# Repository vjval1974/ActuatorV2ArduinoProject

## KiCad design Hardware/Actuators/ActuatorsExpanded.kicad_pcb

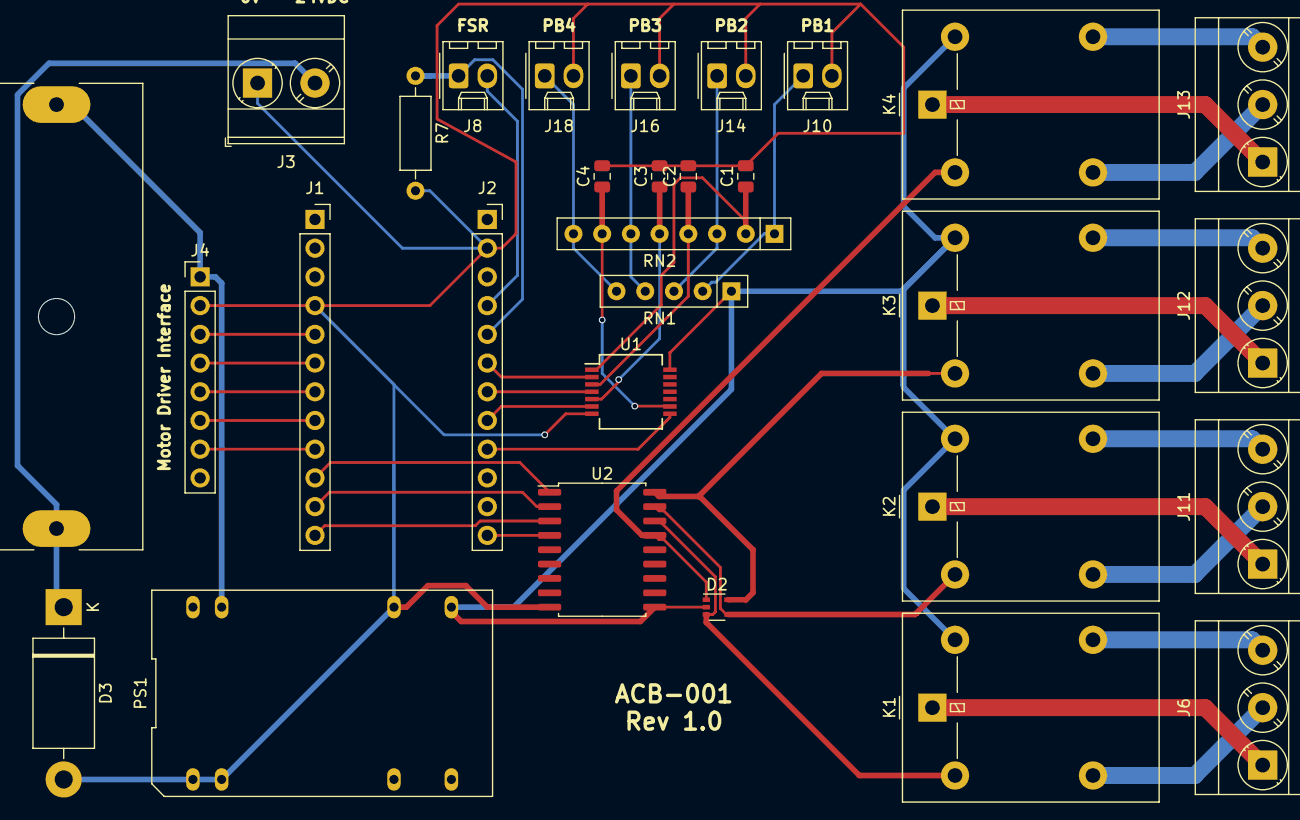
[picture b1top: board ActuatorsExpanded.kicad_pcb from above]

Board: 2 copper layers, 30 parts (0 on the bottom side), 43 nets.

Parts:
C1, C2, C3, C4: 0.1uF; C_0805_2012Metric
D2: MMBD4448HCQW; SOT-353_SC-70-5
D3: 1N5401; D_DO-201AD_P15.24mm_Horizontal
F1: 5A; Fuseholder_Cylinder-6.3x32mm_Schurter_0031-8002_Horizontal_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
J1, J2: Conn_01x12; PinSocket_1x12_P2.54mm_Vertical
J3: Screw_Terminal_01x02; TerminalBlock_Phoenix_MKDS-3-2-5.08_1x02_P5.08mm_Horizontal
J4: Conn_01x08_MountingPin; PinHeader_1x08_P2.54mm_Vertical
J6, J11, J12, J13: Screw_Terminal_01x03; TerminalBlock_Phoenix_MKDS-3-3-5.08_1x03_P5.08mm_Horizontal
J8: Conn_01x02_Female; Molex_KK-254_AE-6410-02A_1x02_P2.54mm_Vertical
J10, J14, J16, J18: Conn_01x02_Male; Molex_KK-254_AE-6410-02A_1x02_P2.54mm_Vertical
K1, K2, K3, K4: G5LE-1; Relay_SPDT_Omron-G5LE-1
PS1: TEN32411WIN; Converter_DCDC_TRACO_TEN32411
R7: 33k; R_Axial_DIN0207_L6.3mm_D2.5mm_P10.16mm_Horizontal
RN1: R_Network04; R_Array_SIP5
RN2: R_Pack04_SIP; R_Array_SIP8
U1: 74HC14; SSOP-14_5.3x6.2mm_P0.65mm
U2: ULN2803A; SOIC-18W_7.5x11.6mm_P1.27mm

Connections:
+5V: D2.2, K1.5, K2.5, K3.5, K4.5, PS1.14, RN1.1, U1.14, U2.10
+24V: F1.1, J4.1, PS1.22
GND: C1.2, C2.2, C3.2, C4.2, D3.2, J1.4, J2.2, J3.1, J4.2, J10.2, J14.2, J16.2, J18.2, PS1.2, PS1.3, PS1.16, R7.2, U1.7, U2.9
unnamed: C1.1, RN2.2, U1.1
unnamed: C2.1, RN2.4, U1.3
unnamed: C3.1, RN2.5, U1.5
unnamed: C4.1, RN2.7, U1.9
unnamed: D2.1, K4.2, U2.15
unnamed: D2.3, K1.2, U2.16
unnamed: D2.4, K2.2, U2.17
unnamed: D2.5, K3.2, U2.18
unnamed: D3.1, F1.2, J3.2
unnamed: J1.5, J4.3
unnamed: J1.6, J4.4
unnamed: J1.7, J4.5
unnamed: J1.8, J4.6
unnamed: J1.9, J4.7
unnamed: J1.10, U2.1
unnamed: J1.11, U2.2
unnamed: J1.12, U2.3
unnamed: J2.4, J8.2
unnamed: J2.5, J8.1, R7.1
unnamed: J2.6, U1.2
unnamed: J2.7, U1.4
unnamed: J2.8, U1.6
unnamed: J2.9, U1.8
unnamed: J2.12, U2.4
unnamed: J6.1, K1.1
unnamed: J6.2, K1.3
unnamed: J6.3, K1.4
unnamed: J10.1, RN1.2, RN2.1
unnamed: J11.1, K2.1
unnamed: J11.2, K2.3
unnamed: J11.3, K2.4
unnamed: J12.1, K3.1
unnamed: J12.2, K3.3
unnamed: J12.3, K3.4
unnamed: J13.1, K4.1
unnamed: J13.2, K4.3
unnamed: J13.3, K4.4
unnamed: J14.1, RN1.3, RN2.3
unnamed: J16.1, RN1.4, RN2.6
unnamed: J18.1, RN1.5, RN2.8

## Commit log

2019-09-01 Initial checkin
2019-09-02 Added motor controller class
2019-09-02 Create classes and object instantiation
2019-09-02 more OO additions
2019-09-03 Removed static variables in method
2019-09-03 Remove static variables from class methods
2019-09-03 Added debug code for state transition
2019-09-03 Set debug constant and debug code for readability
2019-09-04 monitoring settings added
2019-09-04 Pin assignment and pin-mapping fleshed out
2019-09-05 Testing Pushbuttons and wiring
2019-09-09 Tweaks for testing
2019-09-14 partial checkin. calibration code. broken build
2019-10-12 Manaul step through set up for soleniod and vacuum. Updated pins and added output code to drive solenoid/vacuum
2019-10-12 tweaking
2019-12-07 Added Hardware (Kicad)
2019-12-07 Added KiCad Project
2020-10-19 Added links to parts suppliers
2020-10-19 update to proper csv
2020-10-24 Set up CI with Azure Pipelines
    [skip ci]
2020-10-27 update diode array link
2026-05-14 Add CLAUDE.md with architecture and build guidance
    Documents the PlatformIO build/flash workflow, the DEBUG_MODE vs LOG_MODE
    build-flag toggle, and the peripheral Command/State module convention so
    future agents don't have to rediscover them from the source.
    https://claude.ai/code/session_01WQRu2yHUbYqgUTBtQG72rw
2026-05-14 Refactor: scoped enums, const-correctness, eliminate double-construction
    Behaviour-preserving cleanup based on a three-agent code review (architecture,
    embedded/AVR, OO/style). Verified by avr-g++ compile-check against the Arduino
    Leonardo variant (same ATmega32U4, same 16 MHz clock as the Pro Micro target);
    all 11 translation units compile with 0 errors.
    Changes:
    - All enums migrated to `enum class <Name> : uint8_t` and qualified at every
2026-05-14 Add native simulator + browser visualisation
    Reuses the firmware in src/ as the simulation engine: a thin Arduino.h /
    EEPROM.h shim under sim/ lets g++ build the AVR sources natively, a
    physics layer drives the sensor pins each tick, and a Python SSE server
    streams state to an HTML page. The state machine you see in the browser
    is the exact code that flashes to the Pro Micro.
    Layout (sim/):
2026-05-14 Add sim/demo.html — self-contained mobile-friendly preview
    The native simulator needs sim_bin running on a laptop, which a phone on
    a different network can't reach. demo.html is a single static file with
    the state machine re-implemented in ~120 lines of JavaScript, the same
    physics constants as sim/physics.cpp, and a responsive layout that works
    on phone portrait. No server, no compile — open it in any browser.
    Tunings tweaked so a phone user doesn't sit through the firmware's
